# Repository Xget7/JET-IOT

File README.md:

# 🚀 IoT Automation Project Repository for Gates and Alarms 🚪🔒

Welcome to the repository of our exciting IoT automation project for gates, alarms, and more! Here you will find all the code and documentation related to our team's endeavor into the world of Internet of Things (IoT).

## 📋 Description
The main objective of this project is to develop a comprehensive automation system for gates, alarms, and other devices, utilizing cutting-edge IoT technologies. Our solution combines a backend implemented in **Django**, a popular web development platform, with a mobile application developed in **Kotlin** for Android devices. Additionally, we use the **ESP32** as the main microcontroller and have designed a custom PCB that includes a relay and other necessary components.

## 🔑 Key Features
- Gate remote control: You can open, close, and monitor the status of your gate from the comfort of your mobile device. 📱🚪
- Alarm system: We have implemented an alarm system that will instantly notify you of any suspicious events or intrusions. 🚨📢
- IoT integration: Our project allows for the interconnection of various devices, giving you the flexibility to expand your automation system as needed. 🌐🔌
- Django backend: We utilize Django to implement a robust backend that handles business logic, user management, and communication with IoT devices. 💻🌐
- Kotlin MVVM mobile application: The mobile application developed in Kotlin follows the MVVM (Model-View-ViewModel) architecture, providing an intuitive and user-friendly experience. 📱💡

## 🤝 How to Contribute
We would love for you to join our team! If you are interested in contributing to the development of this project, please follow these steps:
1. Fork this repository.
2. Create a branch for your new feature or bug fix.
3. Implement your changes and perform necessary tests.
4. Submit a pull request detailing your modifications.

We hope you are as excited about this IoT project as we are! If you have any questions or suggestions, please feel free to reach out to our team. Enjoy exploring our repository! 🚀😊

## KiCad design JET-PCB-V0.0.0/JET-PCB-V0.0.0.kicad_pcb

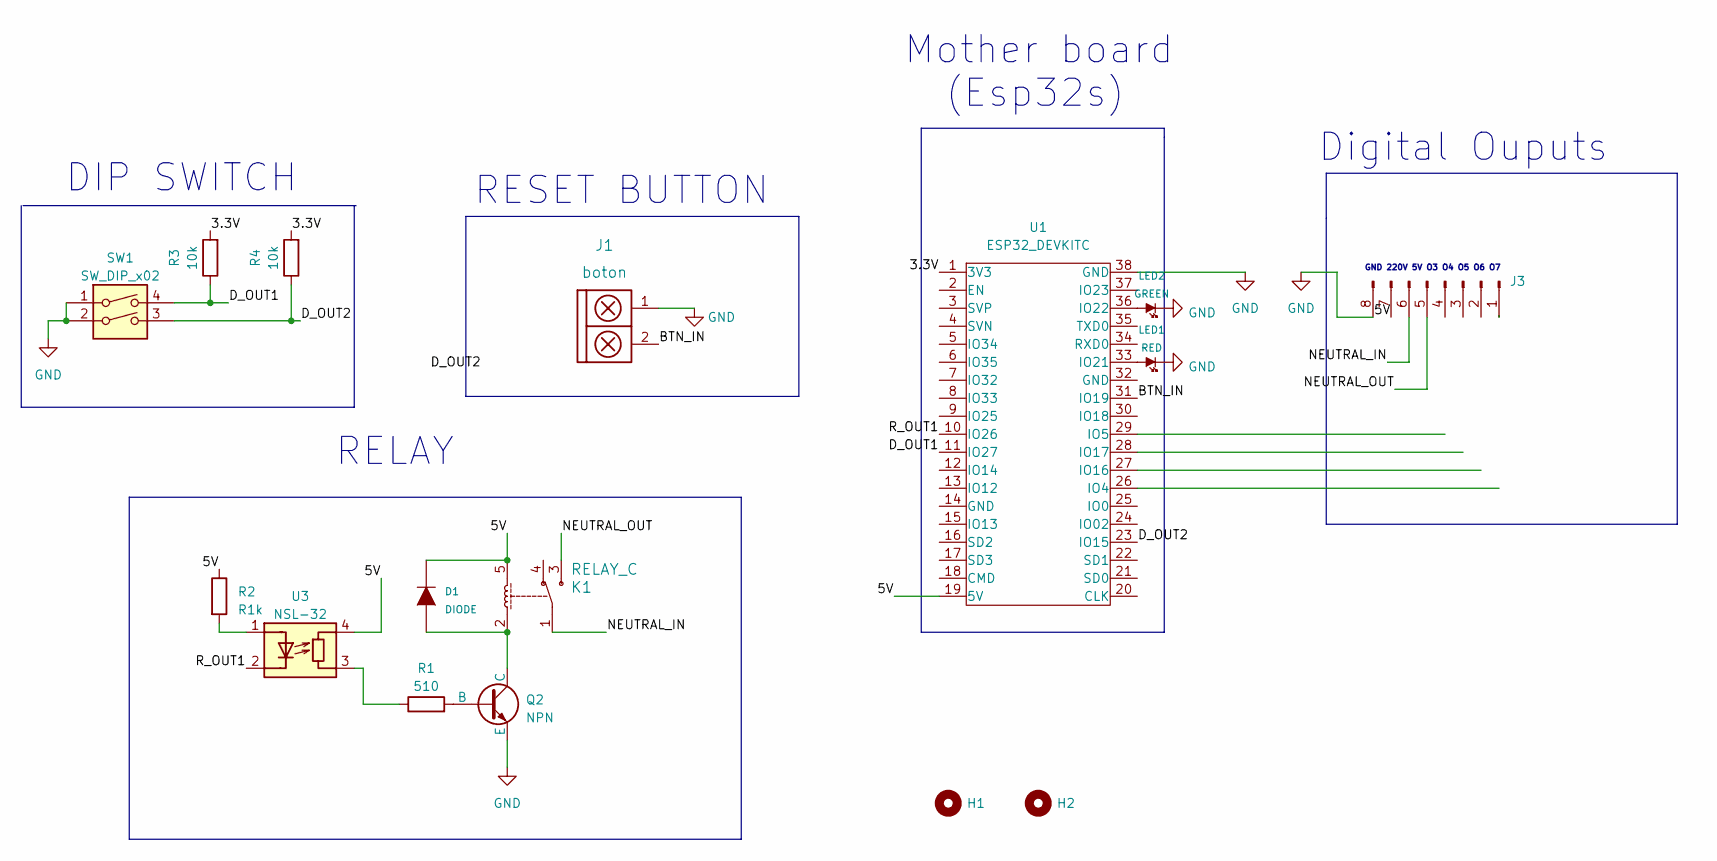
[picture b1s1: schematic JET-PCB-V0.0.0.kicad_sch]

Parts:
D1: DIODE; DO-41
H1, H2: Mounting_Hole; hole_2mm
J1: boton; SW_PUSH_6mm
J3: teclado num 4x4; Pin_Header_Straight_1x08
K1: RELAY_C; Relay_C
LED1: RED; LED_1206
LED2: GREEN; LED_1206
Q2: NPN; SOT23
R1: 510; R_0805
R2: R1k; R_0805
R3, R4: 10k; R_0805
SW1: SW_DIP_x02; Dip_SW_2-300
U1: ESP32_DEVKITC; ESP32S
U3: NSL-32; Luna_NSL-32

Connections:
/3.3V: R3.2, R4.2, U1.1 (3V3)
/5V: D1.2 (K), J3.7, K1.5, R2.1, U1.19 (5V), U3.4 (R)
/BTN_IN: J1.2, U1.31 (IO19)
/D_OUT1: R3.1, SW1.4, U1.11 (IO27)
/D_OUT2: R4.1, SW1.3, U1.23 (IO15)
/NEUTRAL_IN: J3.6, K1.1
/NEUTRAL_OUT: J3.5, K1.3
/R_OUT1: U1.10 (IO26), U3.2 (K)
GND: J1.1, J3.8, LED1.2 (K), LED2.2 (K), Q2.3 (E), SW1.1, SW1.2, U1.38 (GND)
unnamed: D1.1 (A), K1.2, Q2.1 (C)
unnamed: LED1.1 (A), U1.33 (IO21)
unnamed: LED2.1 (A), U1.36 (IO22)
unnamed: Q2.2 (B), R1.2
unnamed: R1.1, U3.3 (R)
unnamed: R2.2, U3.1 (A)

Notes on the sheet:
Digital Ouputs
Mother board (Esp32s)
GND 220V 5V O3 O4 O5 O6 O7
RELAY
DIP SWITCH
RESET BUTTON

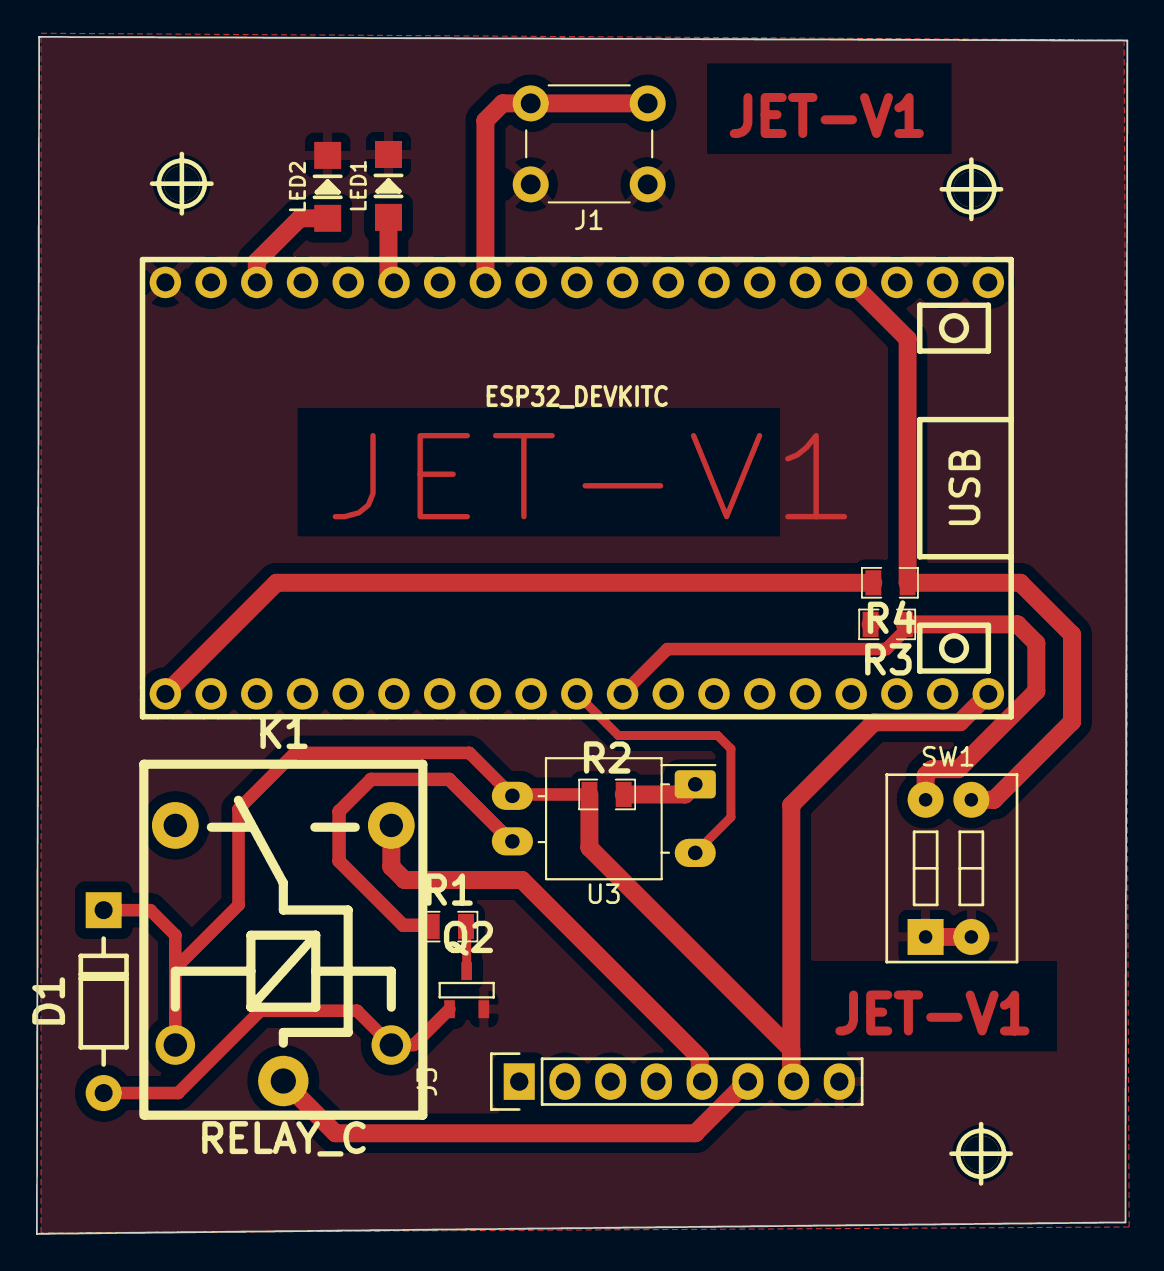
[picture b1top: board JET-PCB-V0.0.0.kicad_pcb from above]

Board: 2 copper layers, 60.6 x 66.5 mm, 17 parts (0 on the bottom side), 15 nets.

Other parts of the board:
H2#2: Mounting_Hole; hole_2mm

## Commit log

2023-05-24 PBC V 0.0.0
2023-05-24 Agrega archivos iniciales
2023-05-29 Fixed
2023-06-20 Arreglo mac sin ":" y mqtt user y server
2023-06-21 MOCK TEST
